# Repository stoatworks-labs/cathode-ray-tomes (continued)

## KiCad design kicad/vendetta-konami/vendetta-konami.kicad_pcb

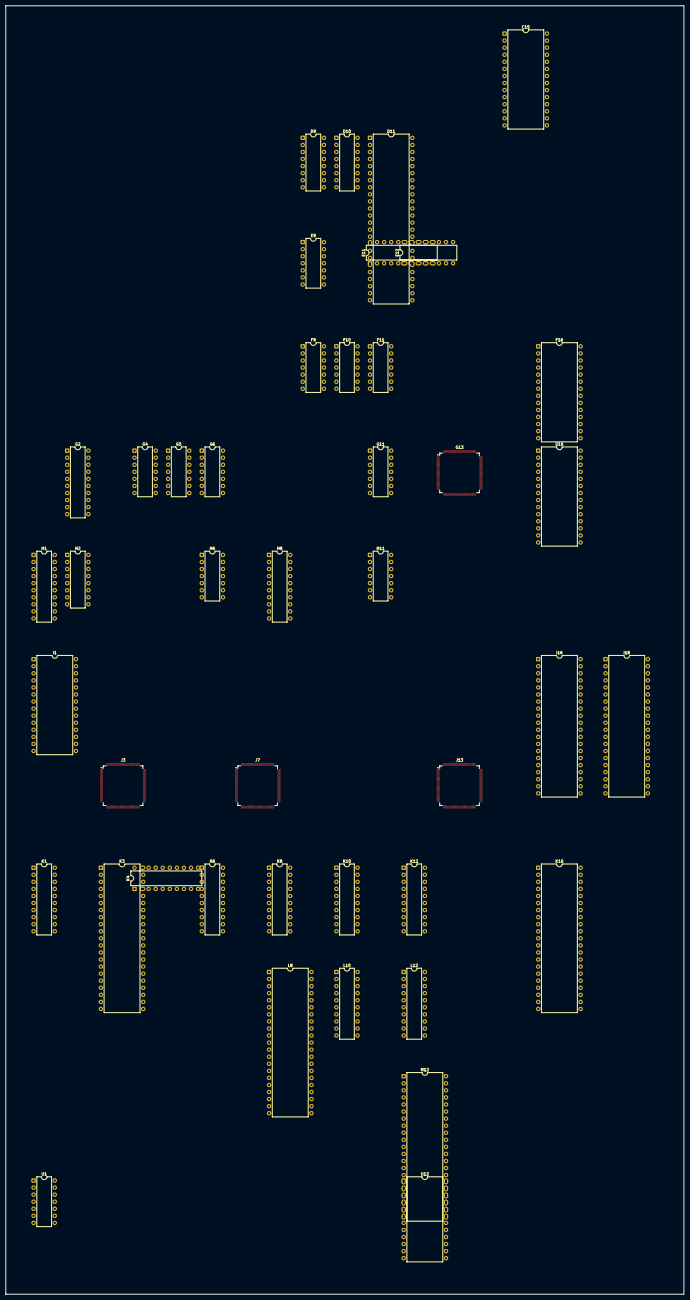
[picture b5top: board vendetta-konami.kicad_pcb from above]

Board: 2 copper layers, 243.9 x 463.4 mm, 43 parts (0 on the bottom side), 315 nets, no tracks yet.

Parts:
C15: DIP-28_W15.24mm
D9: 74LS174; DIP-16_W7.62mm
D10: 74LS138; DIP-16_W7.62mm
D11: DIP-48_W15.24mm
E9: 74LS04; DIP-14_W7.62mm
E11: 74LS273; DIP-20_W7.62mm
E12: 74LS367; DIP-16_W7.62mm
F9, F10: 74LS32; DIP-14_W7.62mm
F11: 74LS04; DIP-14_W7.62mm
F16: MB8464A-10W-15W; DIP-28_W15.24mm
G2: 74LS245; DIP-20_W7.62mm
G4: 74LS04; DIP-14_W7.62mm
G5, G6: 74LS08; DIP-14_W7.62mm
G11: 74LS74; DIP-14_W7.62mm
G13: 052109; TQFP-120_14x14mm_P0.4mm
G16: MB8464A-10W-15W; DIP-28_W15.24mm
H1, H8: 74LS245; DIP-20_W7.62mm
H2: 74LS367; DIP-16_W7.62mm
H6: 74LS32; DIP-14_W7.62mm
H11: 74LS74; DIP-14_W7.62mm
I1: MB8464A-10W-15W; DIP-28_W15.24mm
I16, I18: 955D05-06-07-08; DIP-40_W15.24mm
J3: 053246; TQFP-120_14x14mm_P0.4mm
J7: 053247; TQFP-120_14x14mm_P0.4mm
J13: 051962; TQFP-120_14x14mm_P0.4mm
K1, K4, K6, K8, K10, K12: 74LS374; DIP-20_W7.62mm
K3, K16: 065A08; DIP-42_W15.24mm
L8: 065A08; DIP-42_W15.24mm
L10, L12: 74LS374; DIP-20_W7.62mm
M12: 065A08; DIP-42_W15.24mm
U1: 74LS32; DIP-14_W7.62mm
U12: 051550; DIP-24_W15.24mm

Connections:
/COIN_1: D9.2, U12.15
/COIN_2: D9.5, U12.16
/COIN_CNT_1: U12.20, U12.21
/COIN_CNT_2: U12.22, U12.23
/CPU~RES: D9.1, E11.1, E12.5, G5.4
/CR~CS: D10.11, J7.9
/DS: H6.13, U1.13
/IRQEN: E11.16, G5.5
/MAIN_A0: C15.10, D11.42, F9.12, G2.2, G4.3, G13.66, J3.4, J7.4, J13.88
/MAIN_A1: C15.9, D10.1, D11.41, G13.67, J3.7, J7.7, J13.89
/MAIN_A2: C15.8, D10.2, D11.40, G2.4, G13.68, J3.6, J7.6
/MAIN_A3: C15.7, D10.3, D11.38, G2.5, G13.69
/MAIN_A4: C15.6, G2.6, G13.116
/MAIN_A5: G2.7, G13.115
/MAIN_A6: G2.8, G13.114
/MAIN_A7: G2.9, G13.113
/MAIN_A8: G13.112, H2.2
/MAIN_A9: G13.111, H2.4
/MAIN_A10: G13.110, H2.6
/MAIN_A11: G13.109, H2.10
/MAIN_A12: G13.80, H2.12
/MAIN_DB0: C15.11, D9.14, D11.21, E11.18, G13.56, H1.2, J7.30, J13.79
/MAIN_DB1: C15.12, D9.13, D11.20, E11.17, G13.57, H1.3, J7.29, J13.80
/MAIN_DB2: C15.13, D9.11, D11.19, E11.14, G13.58, H1.4, J7.28, J13.81
/MAIN_DB3: C15.15, D9.6, D11.18, E11.13, G13.59, H1.5, J7.27, J13.82
/MAIN_DB4: C15.16, D9.4, D11.16, E11.8, G13.60, H1.6, J7.26, J13.83
/MAIN_DB5: C15.17, D9.3, D11.15, E11.7, G13.62, H1.7, J7.25, J13.84
/MAIN_DB6: C15.18, D11.14, E11.4, G13.63, H1.8, J7.24
/MAIN_DB7: C15.19, D11.13, E11.3, G13.64, H1.9, J7.23, J13.86
/M~RESET: E12.4, G13.98
/OBJCHA: D9.15, G4.1
/OBJCLK6: J3.12, J7.12, J13.78
/OBJCLK12: J3.10, J7.10, J13.95
/RMRD: D9.10, G13.97, J13.96
/SCR~CLK: F11.8, G13.65, J13.90
/SYS~RES: D11.7, G11.9, G13.55, J3.3, J7.3, J13.92
/VBLK: E9.8, H11.3, H11.11
/VRAM~CS: G13.54, G13.84, J13.97
/objects/EA0: G2.18, I1.10, J3.113
/objects/EA1: G2.17, I1.9, J3.112
/objects/EA2: G2.16, I1.8, J3.110
/objects/EA3: G2.15, I1.7, J3.109
/objects/EA4: H2.11, I1.2, J3.108
/objects/EN0: G2.14, I1.6, J3.105
/objects/EN1: G2.13, I1.5, J3.104
/objects/EN2: G2.12, I1.4, J3.103
/objects/EN3: G2.11, I1.3, J3.102
/objects/EN4: H2.3, I1.25, J3.100
/objects/EN5: H2.5, I1.24, J3.99
/objects/EN6: H2.7, I1.21, J3.98
/objects/EN7: H2.9, I1.23, J3.97
/objects/G2D0: J3.32, J7.119
/objects/G2D1: J3.33, J7.118
/objects/G2D2: J3.34, J7.117
/objects/G2D3: J3.35, J7.116
/objects/G2D4: J3.36, J7.115
/objects/G2D5: J3.37, J7.114
/objects/G2D6: J3.38, J7.113
/objects/G2D7: J3.39, J7.112
/objects/G2D8: J3.40, J7.110
/objects/G2D9: J3.42, J7.109
/objects/G2D10: J3.43, J7.108
/objects/G2D11: J3.44, J7.107
/objects/G2D12: J3.45, J7.105
/objects/G2D13: J3.47, J7.104
/objects/G2D14: J3.48, J7.103
/objects/G2D15: J3.49, J7.102
/objects/G2D16: J3.50, J7.100
/objects/G2D17: J3.52, J7.99
/objects/G2D18: J3.53, J7.98
/objects/G2D19: J3.54, J7.97
/objects/G2D20: J3.55, J7.96
/objects/G2D21: J3.56, J7.95
/objects/LUTD0: H1.18, I1.11, J3.30
/objects/LUTD1: H1.17, I1.12, J3.29
/objects/LUTD2: H1.16, I1.13, J3.28
/objects/LUTD3: H1.15, I1.15, J3.27
/objects/LUTD4: H1.14, I1.16, J3.26
/objects/LUTD5: H1.13, I1.17, J3.25
/objects/LUTD6: H1.12, I1.18, J3.24
/objects/LUTD7: H1.11, I1.19, J3.23
/objects/OBJROMA0: J3.68, K3.10, K16.10, L8.10, M12.10
/objects/OBJROMA1: J3.69, K3.9, K16.9, L8.9, M12.9
/objects/OBJROMA2: J3.70, K3.8, K16.8, L8.8, M12.8
/objects/OBJROMA3: J3.72, K3.7, K16.7, L8.7, M12.7
/objects/OBJROMA4: J3.73, K3.6, K16.6, L8.6, M12.6
/objects/OBJROMA5: J3.74, K3.5, K16.5, L8.5, M12.5
/objects/OBJROMA6: J3.75, K3.4, K16.4, L8.4, M12.4
/objects/OBJROMA7: J3.77, K3.3, K16.3, L8.3, M12.3
/objects/OBJROMA8: J3.78, K3.41, K16.41, L8.41, M12.41
/objects/OBJROMA9: J3.79, K3.40, K16.40, L8.40, M12.40
/objects/OBJROMA10: J3.80, K3.39, K16.39, L8.39, M12.39
/objects/OBJROMA11: J3.82, K3.38, K16.38, L8.38, M12.38
/objects/OBJROMA12: J3.83, K3.37, K16.37, L8.37, M12.37
/objects/OBJROMA13: J3.84, K3.36, K16.36, L8.36, M12.36
/objects/OBJROMA14: J3.85, K3.35, K16.35, L8.35, M12.35
/objects/OBJROMA15: J3.86, K3.34, K16.34, L8.34, M12.34
/objects/OBJROMA16: J3.87, K3.33, K16.33, L8.33, M12.33
/objects/OBJROMA17: J3.88, K3.2, K16.2, L8.2, M12.2
/objects/OBJROMA18: J3.89, K3.1, K16.1, L8.1, M12.1
/objects/OBJROMA19: J3.90, K3.42, K16.42, L8.42, M12.42
/objects/OBJROMD'0: J7.72, K1.2, K6.2, L10.2, L12.2
/objects/OBJROMD'1: J7.73, K1.5, K6.5, L10.5, L12.5
/objects/OBJROMD'2: J7.74, K1.6, K6.6, L10.6, L12.6
/objects/OBJROMD'3: J7.75, K1.9, K6.9, L10.9, L12.9
/objects/OBJROMD'4: J7.77, K1.12, K6.12, L10.12, L12.12
/objects/OBJROMD'5: J7.78, K1.15, K6.15, L10.15, L12.15
/objects/OBJROMD'6: J7.79, K1.16, K6.16, L10.16, L12.16
/objects/OBJROMD'7: J7.80, K1.19, K6.19, L10.19, L12.19
/objects/OBJROMD'8: J7.82, K4.2, K8.2, K10.2, K12.2
/objects/OBJROMD'9: J7.83, K4.5, K8.5, K10.5, K12.5
/objects/OBJROMD'10: J7.84, K4.6, K8.6, K10.6, K12.6
/objects/OBJROMD'11: J7.85, K4.9, K8.9, K10.9, K12.9
/objects/OBJROMD'12: J7.86, K4.12, K8.12, K10.12, K12.12
/objects/OBJROMD'13: J7.87, K4.15, K8.15, K10.15, K12.15
/objects/OBJROMD'14: J7.88, K4.16, K8.16, K10.16, K12.16
/objects/OBJROMD'15: J7.89, K4.19, K8.19, K10.19, K12.19
/objects/ROMD0: K1.3, K3.14
/objects/ROMD1: K1.4, K3.16
/objects/ROMD2: K1.7, K3.18
/objects/ROMD3: K1.8, K3.20
/objects/ROMD4: K1.13, K3.23
/objects/ROMD5: K1.14, K3.25
/objects/ROMD6: K1.17, K3.27
/objects/ROMD7: K1.18, K3.29
/objects/ROMD8: K3.15, K4.3
/objects/ROMD9: K3.17, K4.4
/objects/ROMD10: K3.19, K4.7
/objects/ROMD11: K3.21, K4.8
/objects/ROMD12: K3.24, K4.13
/objects/ROMD13: K3.26, K4.14
/objects/ROMD14: K3.28, K4.17
/objects/ROMD15: K3.30, K4.18
/objects/ROMD16: K6.3, L8.14
/objects/ROMD17: K6.4, L8.16
/objects/ROMD18: K6.7, L8.18
/objects/ROMD19: K6.8, L8.20
/objects/ROMD20: K6.13, L8.23
/objects/ROMD21: K6.14, L8.25
/objects/ROMD22: K6.17, L8.27
/objects/ROMD23: K6.18, L8.29
/objects/ROMD24: K8.3, L8.15
/objects/ROMD25: K8.4, L8.17
/objects/ROMD26: K8.7, L8.19
/objects/ROMD27: K8.8, L8.21
/objects/ROMD28: K8.13, L8.24
/objects/ROMD29: K8.14, L8.26
/objects/ROMD30: K8.17, L8.28
/objects/ROMD31: K8.18, L8.30
/objects/ROMD32: L10.3, M12.14
/objects/ROMD33: L10.4, M12.16
/objects/ROMD34: L10.7, M12.18
/objects/ROMD35: L10.8, M12.20
/objects/ROMD36: L10.13, M12.23
/objects/ROMD37: L10.14, M12.25
/objects/ROMD38: L10.17, M12.27
/objects/ROMD39: L10.18, M12.29
/objects/ROMD40: K10.3, M12.15
/objects/ROMD41: K10.4, M12.17
/objects/ROMD42: K10.7, M12.19
/objects/ROMD43: K10.8, M12.21
/objects/ROMD44: K10.13, M12.24
/objects/ROMD45: K10.14, M12.26
/objects/ROMD46: K10.17, M12.28
/objects/ROMD47: K10.18, M12.30
/objects/ROMD48: K16.14, L12.3
/objects/ROMD49: K16.16, L12.4
/objects/ROMD50: K16.18, L12.7
/objects/ROMD51: K16.20, L12.8
/objects/ROMD52: K16.23, L12.13
/objects/ROMD53: K16.25, L12.14
/objects/ROMD54: K16.27, L12.17
/objects/ROMD55: K16.29, L12.18
/objects/ROMD56: K12.3, K16.15
/objects/ROMD57: K12.4, K16.17
/objects/ROMD58: K12.7, K16.19
/objects/ROMD59: K12.8, K16.21
/objects/ROMD60: K12.13, K16.24
/objects/ROMD61: K12.14, K16.26
/objects/ROMD62: K12.17, K16.28
/objects/ROMD63: K12.18, K16.30
/objects/SCK: J3.66, K1.11, K4.11, K6.11, K8.11, K10.11, K12.11, L10.11, L12.11
/objects/~RDB: H2.13, I1.22, J3.114
/objects/~REG: J3.2, J7.2, U1.11
/objects/~SET0: J3.65, J7.90, K1.1, K4.1
/objects/~SET1: J3.64, J7.92, K6.1, K8.1
/objects/~SET2: J3.63, J7.93, K10.1, L10.1
/objects/~SET3: J3.62, J7.94, K12.1, L12.1
/scroll/CAB1: G13.23, H8.12
/scroll/CAB2: G13.22, H8.11
/scroll/COL2: G13.39, H8.18
/scroll/COL3: G13.40, H8.17
/scroll/COL4: G13.41, H8.16
/scroll/COL5: G13.42, H8.15
/scroll/COL6: G13.43, H8.14
/scroll/COL7: G13.46, H8.13
/scroll/COLB5: H8.6, J13.109
/scroll/COLB6: H8.7, J13.108
/scroll/COLB7: H8.9, J13.107
/scroll/GFXROMA0: G13.35, I16.9, I18.9
/scroll/GFXROMA1: G13.34, I16.8, I18.8
/scroll/GFXROMA2: G13.33, I16.7, I18.7
/scroll/GFXROMA3: G13.32, I16.6, I18.6
/scroll/GFXROMA4: G13.30, I16.5, I18.5
/scroll/GFXROMA5: G13.29, I16.4, I18.4
/scroll/GFXROMA6: G13.28, I16.3, I18.3
/scroll/GFXROMA7: G13.27, I16.2, I18.2
/scroll/GFXROMA8: G13.26, I16.40, I18.40
/scroll/GFXROMA9: G13.25, I16.39, I18.39
/scroll/GFXROMA10: G13.24, I16.38, I18.38
/scroll/GFXROMA11: G13.37, I16.37, I18.37
/scroll/GFXROMA12: G13.38, I16.36, I18.36
/scroll/GFXROMA13: H8.4, I16.35, I18.35
/scroll/GFXROMA14: H8.5, I16.34, I18.34
/scroll/GFXROMA15: H8.2, I16.33, I18.33
/scroll/GFXROMA16: H8.3, I16.32, I18.32
/scroll/GFXROMA17: H8.8, I16.1, I18.1
/scroll/GFXROMD0: I18.13, J13.29
/scroll/GFXROMD1: I18.15, J13.28
/scroll/GFXROMD2: I18.17, J13.27
/scroll/GFXROMD3: I18.19, J13.26
/scroll/GFXROMD4: I18.22, J13.25
/scroll/GFXROMD5: I18.24, J13.24
/scroll/GFXROMD6: I18.26, J13.23
/scroll/GFXROMD7: I18.28, J13.22
/scroll/GFXROMD8: I18.14, J13.21
/scroll/GFXROMD9: I18.16, J13.20
/scroll/GFXROMD10: I18.18, J13.19
/scroll/GFXROMD11: I18.20, J13.18
/scroll/GFXROMD12: I18.23, J13.17
/scroll/GFXROMD13: I18.25, J13.16
/scroll/GFXROMD14: I18.27, J13.13
/scroll/GFXROMD15: I18.29, J13.12
/scroll/GFXROMD16: I16.13, J13.11
/scroll/GFXROMD17: I16.15, J13.10
/scroll/GFXROMD18: I16.17, J13.9
/scroll/GFXROMD19: I16.19, J13.8
/scroll/GFXROMD20: I16.22, J13.7
/scroll/GFXROMD21: I16.24, J13.6
/scroll/GFXROMD22: I16.26, J13.5
/scroll/GFXROMD23: I16.28, J13.4
/scroll/GFXROMD24: I16.14, J13.3
/scroll/GFXROMD25: I16.16, J13.2
/scroll/GFXROMD26: I16.18, J13.120
/scroll/GFXROMD27: I16.20, J13.119
/scroll/GFXROMD28: I16.23, J13.118
/scroll/GFXROMD29: I16.25, J13.117
/scroll/GFXROMD30: I16.27, J13.116
/scroll/GFXROMD31: I16.29, J13.115
/scroll/PREPE: E12.6, G13.90
/scroll/PREPQ: E12.2, G13.89
/scroll/SCRAMA0: F16.10, G13.2, G16.10
/scroll/SCRAMA1: F16.9, G13.120, G16.9
/scroll/SCRAMA2: F16.8, G13.119, G16.8
/scroll/SCRAMA3: F16.7, G13.118, G16.7
/scroll/SCRAMA4: F16.6, G13.117, G16.6
/scroll/SCRAMA5: F16.5, G13.70, G16.5
/scroll/SCRAMA6: F16.4, G13.71, G16.4
/scroll/SCRAMA7: F16.3, G13.72, G16.3
/scroll/SCRAMA8: F16.25, G13.73, G16.25
/scroll/SCRAMA9: F16.24, G13.76, G16.24
/scroll/SCRAMA10: F16.21, G13.77, G16.21
/scroll/SCRAMA11: F16.23, G13.78, G16.23
/scroll/SCRAMA12: F16.2, G13.79, G16.2
/scroll/S~RESET: E12.10, J13.93
/scroll/VD0: G13.20, G16.11
/scroll/VD1: G13.19, G16.12
/scroll/VD2: G13.18, G16.13
/scroll/VD3: G13.17, G16.15
/scroll/VD4: G13.16, G16.16
/scroll/VD5: G13.13, G16.17
/scroll/VD6: G13.12, G16.18
/scroll/VD7: G13.11, G16.19
/scroll/VD8: F16.11, G13.10
/scroll/VD9: F16.12, G13.9
/scroll/VD10: F16.13, G13.8
/scroll/VD11: F16.15, G13.7
/scroll/VD12: F16.16, G13.6
/scroll/VD13: F16.17, G13.5
/scroll/VD14: F16.18, G13.4
/scroll/VD15: F16.19, G13.3
/scroll/ZA1H: G13.50, J13.101
/scroll/ZA2H: G13.51, J13.100
/scroll/ZA4H: G13.52, J13.99
/scroll/ZB1H: G13.47, J13.106
/scroll/ZB2H: G13.48, J13.103
/scroll/ZB4H: G13.49, J13.102
/scroll/~BE: G13.53, J13.98
/scroll/~RCS1: F16.20, G13.93
/scroll/~ROE1: F16.22, G13.95
/scroll/~ROE2: G13.96, G16.22
/scroll/~RWE1: F16.27, G13.107
/scroll/~RWE2: G13.108, G16.27
/scroll/~VSYNC: H11.10, J13.72
/~CPU: G2.19, H2.1, H2.15, J3.116
/~HSYNC: G6.5, J13.73
/~RD: G13.85, H1.1, H2.14, J13.87
/~VBLANK: J3.119, J13.69
/~WR: C15.27, D11.37
/~XSYNC: G6.6, J3.8, J7.8
unnamed: C15.26, E9.6
unnamed: D9.9, D10.15
unnamed: D10.14, E11.11
unnamed: D11.27, E9.9
unnamed: F10.1, G4.4
unnamed: F9.13, F10.2
unnamed: F11.9, F11.13
unnamed: F11.12, G11.11
unnamed: G11.12, G11.13, U12.10
unnamed: G5.6, H11.4
unnamed: G6.4, H11.9
unnamed: H6.11, I1.27
unnamed: G4.2, J3.9
VCC: C15.20, C15.28, D10.6, D11.17, D11.23, D11.39, D11.43, E12.16, F16.26, F16.28, G2.1, G11.10, G13.14, G13.44, G13.74, G13.104, G16.26, G16.28, H2.16, H11.1, H11.13, I1.26, I1.28, I16.21, I18.21, J3.5, J3.16, J3.46, J3.60, J3.76, J3.106, J3.120, J7.5, J7.16, J7.46, J7.60, J7.70, J7.76, J7.106, J7.120, J13.14, J13.44, J13.74, J13.104, K3.22, K3.32, K16.22, K16.32, L8.22, L8.32, M12.22, M12.32
VSS: C15.14, D11.6, D11.22, D11.28, E12.1, E12.8, F16.14, G13.1, G13.15, G13.21, G13.31, G13.36, G13.45, G13.61, G13.75, G13.91, G13.105, G16.14, G16.20, H2.8, H8.1, H8.19, H11.2, H11.12, I1.14, I1.20, I16.10, I16.11, I16.12, I16.30, I16.31, I18.10, I18.11, I18.12, I18.30, I18.31, J3.91, J3.101, J3.111, J3.117, J3.118, J7.1, J7.11, J7.21, J7.31, J7.41, J7.51, J7.61, J7.62, J7.63, J7.64, J7.65, J7.66, J7.67, J7.68, J7.69, J7.71, J7.81, J7.91, J7.101, J7.111, J13.1, J13.15, J13.31, J13.45, J13.61, J13.75, J13.91, J13.94, J13.105, J13.110, J13.111, J13.112, J13.113, J13.114, K3.11, K3.12, K3.13, K3.31, K16.11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

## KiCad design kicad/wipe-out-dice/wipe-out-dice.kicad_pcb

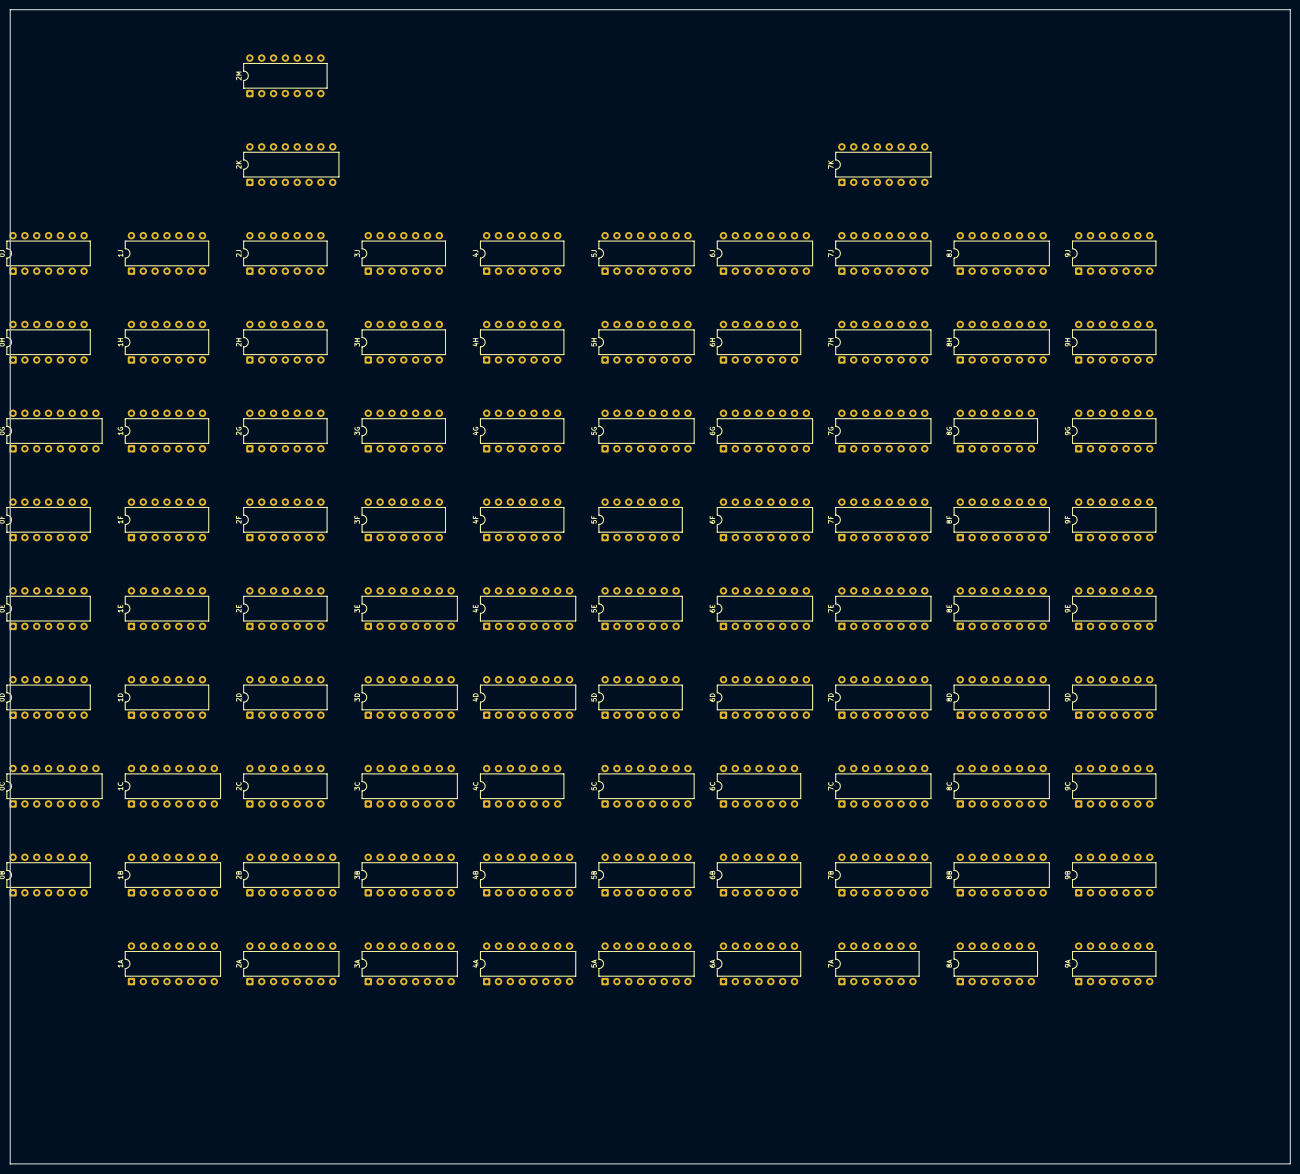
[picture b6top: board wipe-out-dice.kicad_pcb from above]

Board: 2 copper layers, 274.6 x 247.6 mm, 92 parts (0 on the bottom side), 339 nets, no tracks yet.

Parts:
0B, 2C, 2H, 4C, 6A, 6C, 8A: 7404; DIP-14_W7.62mm
0C, 0G, 1C, 2K, 5H, 5J, 6J, 7B, 7K, 8F: 74S112; DIP-16_W7.62mm
0D: 7437; DIP-14_W7.62mm
0E, 3H: 7486; DIP-14_W7.62mm
0F, 0H, 1H, 2M, 3J, 4G, 6H, 9D, 9E: 7402; DIP-14_W7.62mm
0J, 3G, 7A, 9B, 9C: 7420; DIP-14_W7.62mm
1A, 1B, 2A, 2B, 3A, 3B, 3C, 3D, 3E, 6D, 6E, 6F, 6G, 7C, 7D, 7E, 7J, 8D, 8E: 74161; DIP-16_W7.62mm
1D, 1F, 2D, 4H, 5E, 6B, 8G, 9A, 9F, 9G, 9H, 9J: 7400; DIP-14_W7.62mm
1E, 1J, 3F, 4F, 4J, 5F: 7427; DIP-14_W7.62mm
1G, 2G, 2J: 7408; DIP-14_W7.62mm
2E, 2F, 5D: 7421; DIP-14_W7.62mm
4A, 4B, 5B, 5C: 74153; DIP-16_W7.62mm
4D, 7G: 82S123; DIP-16_W7.62mm
4E: 74166; DIP-16_W7.62mm
5A, 5G, 8B, 8C, 8J: 74174; DIP-16_W7.62mm
7F, 7H, 8H: 74157; DIP-16_W7.62mm

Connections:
+5V: 0B.14, 0C.16, 0D.14, 0E.14, 0F.14, 0G.16, 0H.14, 0J.14, 1A.16, 1B.16, 1C.16, 1D.14, 1E.14, 1F.14, 1G.14, 1H.14, 1J.14, 2A.16, 2B.16, 2C.14, 2D.14, 2E.14, 2F.14, 2G.14, 2H.14, 2J.14, 2K.16, 2M.14, 3A.16, 3B.16, 3C.16, 3D.16, 3E.16, 3F.14, 3G.14, 3H.14, 3J.14, 4A.16, 4B.16, 4C.14, 4D.16, 4E.16, 4F.14, 4G.14, 4H.14, 4J.14, 5A.16, 5B.16, 5C.16, 5D.14, 5E.14, 5F.14, 5G.16, 5H.16, 5J.16, 6A.14, 6B.14, 6C.14, 6D.16, 6E.16, 6F.16, 6G.16, 6H.14, 6J.16, 7A.14, 7B.16, 7C.16, 7D.16, 7E.16, 7F.16, 7G.16, 7H.16, 7J.16, 7K.16, 8A.14, 8B.16, 8C.16, 8D.16, 8E.16, 8F.16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
GND: 0B.7, 0C.8, 0D.7, 0E.7, 0F.7, 0G.8, 0H.7, 0J.7, 1A.3, 1A.4, 1A.5, 1A.8, 1B.5, 1B.8, 1C.8, 1D.7, 1E.7, 1F.7, 1G.7, 1H.7, 1J.7, 2A.3, 2A.4, 2A.5, 2A.8, 2B.3, 2B.8, 2C.7, 2D.7, 2E.7, 2F.7, 2G.7, 2H.7, 2J.7, 2K.8, 2M.7, 3A.3, 3A.5, 3A.8, 3B.3, 3B.5, 3B.8, 3C.3, 3C.5, 3C.8, 3D.3, 3D.5, 3D.8, 3E.3, 3E.4, 3E.5, 3E.6, 3E.8, 3F.7, 3G.7, 3H.7, 3J.7, 4A.1, 4A.8, 4A.15, 4B.1, 4B.8, 4C.7, 4C.13, 4D.8, 4D.15, 4E.1, 4E.2, 4E.3, 4E.4, 4E.5, 4E.8, 4E.14, 4F.7, 4G.7, 4H.7, 4J.7, 5A.8, 5B.8, 5C.1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
VCC: 0C.2, 0C.3, 0C.4, 0C.10, 0C.15, 0G.4, 0G.10, 1A.1, 1A.6, 1A.7, 1A.10, 1B.1, 1C.4, 1C.10, 1C.14, 1C.15, 2A.1, 2A.7, 2A.10, 2B.1, 3A.1, 3A.6, 3A.10, 3B.1, 3B.6, 3B.10, 3C.1, 3C.6, 3C.10, 3D.1, 3D.6, 3D.10, 3E.1, 5A.1, 5H.4, 5H.10, 5H.14, 5H.15, 5J.4, 5J.10, 5J.14, 5J.15, 6D.1, 6D.10, 6E.1, 6E.10, 6F.1, 6F.10, 6G.1, 6G.10, 6J.3, 6J.10, 7B.4, 7B.14, 7C.1, 7D.1, 7E.1, 7J.1, 8B.1, 8C.1, 8D.1, 8E.1, 8J.1
_1BEGD: 8A.8, 9C.1, 9C.2
_1BLGD: 8A.10, 8B.13, 9A.1, 9J.9
_1BLGE: 3H.12, 8B.12, 9C.4, 9J.2
_1BVAF: 2J.10, 2J.13, 8A.12, 9G.1, 9G.5
_1EBCA: 7C.9, 8B.15
_1NCFG: 2H.8, 5H.2
_1PCX3: 5A.4, 6B.11
_1PGCC: 5E.12, 8C.15
_1PGSB: 5H.3, 6A.6
_1TCKG: 2M.11, 6A.2
_1TECC: 0B.10, 1C.2, 1C.3
_1TEG7: 0H.6, 1J.5, 2C.8, 2F.5, 3F.4, 8H.6
_1TLCC: 0B.12, 1C.11, 1C.12, 7C.7
_1TLG7: 0H.8, 1J.13, 2C.10, 2F.9, 3F.2, 8H.13
_1TNSC: 2H.6, 4A.14, 4B.14
_1TPSC: 2H.4, 5B.14, 5C.14
_1TQ05: 0C.5, 0D.1, 0D.2, 9F.9
_2KQEA: 6J.1, 9D.1
_2KQEL: 8F.1, 9D.10, 9D.11
_2KQLN: 8F.13, 9D.4, 9D.12
_2THSC: 0D.11, 0G.13, 1C.13, 2K.1, 2K.13
_2TQ05: 0C.13, 0D.6, 0G.1, 1C.1, 5H.1, 6J.13, 7B.1, 7B.13, 7K.1, 7K.13
_5BDEC: 8G.5, 8H.7
_5BDGD: 9J.4, 9J.8
_5BDGR: 9J.3, 9J.5
_5BDLC: 8G.12, 8H.12
_5BDRD: 8D.5, 8F.7
_5BDRR: 7D.5, 8F.6
_5BDSD: 8F.10, 8G.8
_5BDSL: 8F.15, 8G.6
_5BDSR: 8F.4, 8G.3
_5BDSU: 8F.14, 8G.11
_5BECB: 8A.4, 8C.3
_5BECL: 7E.9, 9C.6
_5BEGA: 8C.2, 8C.4, 9A.5, 9B.5
_5BEGB: 8C.5, 8C.6, 9B.4
_5BEGC: 8C.7, 8C.11, 9B.2
_5BEGD: 8A.9, 8C.10, 9A.4, 9B.1
_5BLCB: 8A.6, 8B.3
_5BLCL: 8E.9, 9A.3
_5BLGA: 8B.2, 8B.4, 9A.9, 9B.9
_5BLGB: 8B.5, 8B.6, 9B.10
_5BLGC: 8B.7, 8B.11, 9B.12
_5BLGD: 8A.11, 8B.10, 9A.10, 9B.13
_5BSCG: 9E.3, 9H.3
_5BVAD: 9A.11, 9C.10
_5BVAF: 3G.10, 8A.13, 9C.8, 9E.5, 9E.9
_5EBCA: 6A.12, 9D.3
_5EBEA: 6B.3, 7A.5
_5EBEB: 6B.6, 7A.4
_5EBEC: 6B.8, 7A.1, 7A.2
_5EBIP: 7A.9, 7B.6, 7J.10
_5EBOP: 6J.7, 7A.10
_5EBUZ: 6J.15, 7A.12, 7A.13, 7B.7, 7D.9, 7J.9, 8D.9, 9C.12
_5KAAA: 3G.12, 4G.10, 9E.6
_5KAAB: 3G.13, 4G.13, 9E.8
_5KAAE: 8J.3, 9G.3
_5KAAF: 8J.4, 9G.6
_5KABC: 6A.8, 9D.5, 9F.12
_5KABD: 6A.10, 9D.9, 9F.13
_5KABE: 8J.2, 9F.5, 9H.4
_5KABF: 8J.5, 9F.4, 9H.10
_5KACG: 3F.1, 4F.3, 9F.2, 9G.8
_5KACH: 3F.3, 3F.11, 9F.1, 9G.11
_5KBCH: 6H.10, 9H.5
_5KBDG: 6H.13, 9H.9
_5NCAD: 3J.12, 4J.12
_5NCCC: 1F.11, 3E.7, 3E.10, 4E.9
_5NCCE: 2C.12, 4E.6
_5NCFA: 3J.9, 4J.8
_5NCFB: 3J.8, 4H.6, 9H.12
_5NCFE: 3J.11, 4H.8, 9H.13
_5NCFG: 2H.9, 3J.4
_5NCG2: 4C.10, 5D.10
_5NCG3: 4C.8, 5D.4
_5NCGA: 4H.3, 5D.1, 5D.2, 5D.12, 5D.13
_5NCS0: 4C.6, 4D.12
_5NCS1: 4C.4, 4D.13
_5NCS2: 4C.2, 4D.14
_5PCBB: 5F.13, 7K.7
_5PCLB: 2K.6, 4F.9
_5PCRB: 2K.7, 5F.5
_5PCS3: 6C.12, 8F.2, 8F.12
_5PCTB: 5F.9, 7K.6
_5PCX3: 2M.10, 6B.12, 6B.13
_5PDEC: 5E.8, 9C.5
_5PDGS: 2M.9, 3H.10, 5B.1, 5B.15, 5E.5, 5E.9, 6J.6
_5PDLC: 5E.6, 9A.2
_5PDPS: 5E.10, 6C.10
_5PGCC: 4G.6, 5J.6
_5PGCE: 5J.7, 6H.2
_5PGCG: 1E.2, 4J.1, 4J.11, 5H.7
_5PGSB: 5E.3, 6A.5
_5PGSC: 5H.6, 9E.11
_5PGSR: 3A.9, 3B.9, 3C.9, 3D.9, 5E.11, 7B.10
_5PJC1: 5A.13, 6A.4
_5PKE5: 6C.6, 7K.4, 7K.10
_5PKE8: 6C.2, 7K.14, 7K.15
_5PKL5: 2K.4, 2K.10, 6C.8
_5PKL8: 2K.14, 2K.15, 6C.4
_5TCBL: 0H.13, 4H.12
_5TCKG: 6A.1, 8H.1, 9E.2, 9J.11
_5TEC0: 2C.2, 8H.5
_5TEC5: 0C.11, 2C.4
_5TEC8: 0G.15, 1B.3, 1B.4, 1B.6, 1C.6
_5TECC: 0B.11, 1A.9, 1B.9, 1D.3
_5TECD: 1D.6, 1D.10, 1D.12
_5TEG7: 1D.8, 1G.10, 1J.9, 2C.9, 3F.10, 8H.3
_5TEG8: 1D.11, 7E.7, 7E.10
_5TELA: 0F.3, 1F.3
_5TGBG: 1H.6, 4J.6
_5TGLG: 1H.2, 1J.6
_5TGRG: 1H.3, 1J.8
_5TGTG: 1H.5, 1J.12
_5THBG: 0G.6, 2M.2
_5THPG: 0J.8, 1H.12
_5THSC: 0C.7, 1F.9
_5TLC0: 2C.6, 8H.14
_5TLC8: 0G.14, 1C.7, 2B.4, 2B.5, 2B.6, 3G.4, 3G.5, 7C.10
_5TLCC: 0B.13, 2A.9, 2B.9, 2D.3
_5TLCD: 2D.6, 2D.10, 2D.12
_5TLG7: 1G.13, 2C.11, 2D.8, 4F.4, 4J.5, 8H.10
_5TLG8: 2D.11, 8E.7, 8E.10
_5TLLA: 0F.6, 1F.6
_5TLLG: 2H.2, 5B.2, 5C.2
_5TNSC: 2H.5, 3J.1
_5TPSC: 1E.12, 2H.3
_5TVBG: 0G.7, 2M.5
_5TVPG: 0J.6, 1H.9
_5TVSC: 1F.10, 3G.6
_5VDAC: 3G.9, 4F.12
_5VDAE: 4H.11, 8J.13
_5VDAF: 2H.13, 8J.12
_6KQCA: 9D.6, 9D.8, 9F.8
_6THSC: 0D.8, 0D.12, 0D.13, 2A.2, 2B.2, 3E.2, 6E.2, 6F.2, 7C.2, 8B.9, 8D.2, 8E.2
_6TQ05: 0D.3, 0D.4, 0D.5, 1A.2, 1B.2, 3A.2, 3B.2, 3C.2, 3D.2, 5G.9, 6D.2, 6G.2, 7D.2, 7E.2, 7J.2, 8C.9, 8J.9, 9D.2
_7KQPD: 5A.9, 9D.13
_9X7PT: 3A.4, 3B.4, 3C.4, 3D.4
_BDEC: 8G.2, 8H.4
_BDLC: 8G.9, 8H.9
_BDRD: 8D.3, 8D.4, 8D.6, 8F.9, 9J.10
_BDRR: 7D.3, 7D.4, 7D.6, 8F.5, 9J.1
_BECA: 7D.7, 7D.10, 7E.15
_BECB: 7D.15, 8A.3
_BGS0: 7F.9, 7G.10
_BGS1: 7F.7, 7G.11
_BGS2: 7F.4, 7G.12
_BGS3: 7G.13, 9J.6
_BLCA: 8D.7, 8D.10, 8E.15
_BLCB: 8A.5, 8D.15
_BPE0: 7G.5, 7H.13
_BPE1: 7G.6, 7H.10
_BPE2: 7G.7, 7H.6
_BPE3: 7G.9, 7H.3
_BPL0: 7G.1, 7H.14
_BPL1: 7G.2, 7H.11
_BPL2: 7G.3, 7H.5
_BPL3: 7G.4, 7H.2
_BPS0: 7E.3, 7H.12, 8E.3
_BPS1: 7E.4, 7H.9, 8E.4
_BPS2: 7E.5, 7H.7, 8E.5
_BPS3: 7E.6, 7H.4, 8E.6
_BPSC: 3H.11, 7F.1, 7H.1
_BPSV: 3H.8, 3H.13
_BSC3: 7F.6, 7J.13
_BSC4: 7J.12, 9H.1, 9H.2
_BSCD: 8H.15, 9E.1
_BVAA: 9A.6, 9A.12
_BVAB: 9A.8, 9A.13
_BVAC: 9B.6, 9C.9
_BVAE: 9B.8, 9C.13
_BXYZ: 7F.10, 9H.11
_EBC2: 6J.12, 7B.2, 7C.12
_EBCA: 2M.12, 6A.13, 7A.8, 8B.14
_EBCC: 7B.12, 7C.15
_EBIP: 6B.2, 7B.5
_EBOP: 6B.5, 6J.9
_EBUZ: 6B.9, 7B.9, 9E.12
_KAAC: 5G.13, 9E.4
_KAAD: 5G.14, 9E.10
_KAAG: 2J.8, 8J.6
_KAAH: 2J.11, 8J.11
_KABC: 5G.12, 6A.9, 6H.9
_KABD: 5A.3, 5G.15, 6A.11, 6H.12
_KABG: 6H.11, 8J.7, 9G.9
_KABH: 6H.8, 8J.10, 9G.12
_KACA: 8G.1, 8G.4, 9H.6
_KACB: 8G.10, 8G.13, 9H.8
_KACE: 6J.11, 9F.6
_KACF: 7B.3, 7J.7, 9F.11
_KADG: 7B.11, 9F.3
_KAYA: 2M.13, 9F.10
_KXYA: 9E.13, 9G.10, 9G.13
_NCB0: 3D.14, 4B.6
_NCB1: 3D.13, 4A.10
_NCB2: 3D.12, 4A.6
_NCBA: 3D.7, 4F.6
_NCBC: 3D.15, 4F.5, 4H.10, 4J.4, 4J.10
_NCC1: 1F.13, 3E.13, 4D.10
_NCC2: 3E.12, 4D.11
_NCC3: 1F.12, 3E.11, 4H.1
_NCCE: 2C.13, 3E.9, 4G.1
_NCFC: 3J.5, 3J.10
_NCFF: 3J.6, 3J.13
_NCG2: 4C.11, 4D.3
_NCG3: 4C.9, 4D.4
_NCG4: 4D.5, 4H.2
_NCG5: 4D.6, 4E.10
_NCG6: 4D.7, 5D.9
_NCG7: 4D.9, 5D.5
_NCH6: 4E.11, 5D.8
_NCH7: 4E.12, 5D.6
_NCL0: 3A.14, 4B.3
_NCL1: 3A.13, 4A.13
_NCL2: 3A.12, 4A.3
_NCLA: 3A.7, 3F.6
_NCLC: 1J.4, 3A.15, 3F.5, 4H.5, 4J.13
_NCR0: 3C.14, 4B.4
_NCR1: 3C.13, 4A.12
_NCR2: 3C.12, 4A.4
_NCRA: 3C.7, 3F.8
_NCRC: 1J.10, 3C.15, 3F.9, 4H.4, 4J.2
_NCS0: 4B.7, 4C.5
_NCS1: 4A.9, 4C.3
_NCS2: 4A.7, 4C.1
_NCSC: 4B.9, 4E.15
_NCT0: 3B.14, 4B.5
_NCT1: 3B.13, 4A.11
_NCT2: 3B.12, 4A.5
_NCTA: 3B.7, 3F.12
_NCTC: 1J.2, 3B.15, 3F.13, 4H.9, 4J.9
_NCVD: 4E.13, 4F.13
_PCB1: 5B.10, 6D.13
_PCB2: 5B.6, 6D.12
_PCB3: 5C.10, 6D.11
_PCBB: 6D.9, 7K.9
_PCBC: 5F.2, 6D.15
_PCBE: 5C.6, 5F.12, 6D.7
_PCL1: 5B.13, 6E.13
_PCL2: 5B.3, 6E.12
_PCL3: 5C.13, 6E.11
_PCLB: 2K.5, 6E.9
_PCLC: 4F.10, 6E.15
_PCLE: 4F.8, 5C.3, 6E.7
_PCR1: 5B.12, 6F.13
_PCR2: 5B.4, 6F.12
_PCR3: 5C.12, 6F.11
_PCRB: 2K.9, 6F.9
_PCRC: 5F.4, 6F.15
_PCRE: 5C.4, 5F.6, 6F.7
_PCS1: 5A.11, 5B.9
_PCS2: 5A.6, 5B.7
_PCS3: 2M.8, 5C.9, 6C.13, 8F.3, 8F.11
_PCSE: 0J.1, 0J.13, 5C.7
_PCT1: 5B.11, 6G.13
_PCT2: 5B.5, 6G.12
_PCT3: 5C.11, 6G.11
_PCTB: 6G.9, 7K.5
_PCTC: 5F.10, 6G.15
_PCTE: 5C.5, 5F.8, 6G.7
_PDGS: 6J.5, 7F.3
_PDPS: 3H.9, 5A.2, 5E.4, 6C.11
_PDS1: 5A.10, 7F.11
_PDS2: 5A.7, 7F.5
_PDS3: 5A.5, 7F.2
_PGCB: 4G.5, 5J.3, 8C.12
_PGCC: 5J.5, 8C.14
_PGCD: 4G.4, 5J.11, 6H.3
_PGCE: 5E.2, 5J.9, 6H.6
_PGCF: 5H.11, 6H.1
_PGCH: 5H.12, 6H.4
_PGSC: 2M.3, 2M.6, 5E.13, 5G.1, 5H.5, 5J.2, 5J.12, 6H.5, 6J.4, 6J.14, 7B.15, 7G.14
_PJC0: 5A.12, 5A.14
_PJC1: 5A.15, 6A.3
_PKE5: 5G.7, 6C.5
_PKE8: 5G.2, 6C.1
_PKL5: 5G.10, 6C.9
_PKL8: 5G.5, 6C.3
_TCSC: 1F.8, 8J.14
_TE43: 0J.5, 3H.3
_TE75: 0E.6, 1E.3, 1G.1
_TE76: 0E.3, 1E.5, 1G.2
_TEC0: 1A.14, 2C.1, 4E.7, 8H.2
_TEC3: 1A.11, 1B.10, 3H.1
_TEC4: 0F.2, 1B.14, 2E.13, 2F.2, 3H.2
_TEC5: 0C.12, 0E.4, 1B.13, 2C.3, 2E.10
_TEC6: 0E.1, 1B.12, 2E.9, 2F.4, 4B.12, 4B.13
_TEC7: 0E.2, 0E.5, 1B.11, 1D.9, 4B.10, 4B.11
_TEC8: 0C.14, 1C.5, 1D.4, 1D.13, 1E.4, 4B.15, 5G.3
_TECA: 1A.15, 1B.7, 1D.1, 1F.2, 2E.12
_TECB: 1B.15, 1D.2, 1D.5, 2J.12
_TEKG: 0H.5, 1G.3, 2G.2, 9J.13
_TELG: 0J.4, 1E.6, 1F.1, 1G.9, 1J.1, 4J.3, 5F.1, 5F.11
_TEVL: 0F.1, 0F.9, 0G.2, 0G.3, 2J.1
_THBG: 0F.8, 0G.5, 0J.2, 2F.1
_THBL: 0F.10, 0H.12
_THCH: 2G.3, 4G.8
_THCL: 2E.6, 2G.1, 2G.5
_THLG: 1H.4, 1H.11, 2J.5
_THLN: 2J.6, 4F.1, 9G.4
_THPD: 1H.13, 4G.12
_THSC: 0C.9, 0D.9, 0D.10
_THYZ: 2G.13, 2M.1
_TL43: 0J.9, 3H.6
_TL75: 0E.11, 1E.11, 1G.4
_TL76: 0E.8, 1E.9, 1G.5
_TLC0: 2A.14, 2C.5, 8H.11
_TLC2: 2A.12, 3G.1
_TLC3: 2A.11, 2B.10, 3H.4, 6B.1
_TLC4: 0F.5, 2B.14, 2E.2, 2F.13, 3H.5, 6B.4
_TLC5: 0E.13, 2B.13, 2E.4, 4G.2
_TLC6: 0E.10, 2B.12, 2E.5, 2F.10, 6B.10
_TLC7: 0E.9, 0E.12, 2B.11, 2D.9
_TLC8: 1C.9, 1E.10, 2A.6, 2D.5, 2D.13, 5G.4, 5H.13, 5J.1, 5J.13
_TLCA: 1F.5, 2A.15, 2B.7, 2D.1, 2E.1
_TLCB: 2B.15, 2D.2, 2D.4, 2J.9, 3G.2
_TLHL: 0F.4, 0F.12, 0G.11, 0G.12, 2J.4
_TLKG: 0H.9, 1G.6, 2G.9, 4A.2, 4B.2, 9J.12
_TLLG: 0J.10, 1E.8, 1F.4, 1G.12, 1J.3, 1J.11, 2H.1, 4F.11, 4G.3, 5F.3
_TNSA: 0H.4, 3J.2
_TNSB: 0H.10, 3J.3
_TPHR: 2G.11, 7K.2, 7K.12
_TPHS: 2F.6, 5G.6
_TPSA: 1E.13, 1G.8
_TPSB: 1E.1, 1G.11
_TPVR: 2G.6, 2K.2, 2K.12
_TPVS: 2F.8, 5G.11
_TVBG: 0F.11, 0G.9, 0J.12, 2F.12
_TVBL: 0F.13, 0H.11
_TVCH: 2G.8, 4G.11
_TVCL: 2E.8, 2G.10, 2G.12
_TVLG: 1H.1, 1H.8, 2J.2
_TVLN: 2J.3, 4F.2, 9G.2
_TVPD: 1H.10, 4G.9
_TVYZ: 2G.4, 2M.4
_VDAD: 3G.8, 4H.13

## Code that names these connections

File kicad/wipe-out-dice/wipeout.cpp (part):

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#define _1TQ05  "0C", 5
#define _6TQ05  "0D", 3  
#define _2TQ05  "0D", 6  
#define _THSC   "0C", 9  //HSYNC 
#define _5THSC  "0C", 7  //HSYNC
#define _6THSC  "0D", 8
#define _2THSC  "0D", 11
#define _TCSC   "1F", 8  //COMP SYNC

  //Timing/Syncing/Blanking
#define _TECA   "1A", 15
#define _TEC0   "1A", 14
#define _TEC3   "1A", 11
#define _TEC4   "1B", 14
#define _TEC5   "1B", 13
#define _TEC6   "1B", 12
#define _TEC7   "1B", 11
#define _TECB   "1B", 15
#define _5TEC0  "2C", 2
#define _5TEC5  "2C", 4
#define _5TECC  "1D", 3
#define _1TECC  "0B", 10
#define _TEC8   "1C", 5
#define _5TEC8  "1C", 6
#define _5TECD  "1D", 6
#define _5TEG7  "1D", 8
#define _5TEG8  "1D", 11
#define _1TEG7  "2C", 8

#define _TLCA   "2A", 15 
#define _TLC0   "2A", 14
#define _TLC2   "2A", 12
#define _TLC3   "2A", 11
#define _TLC4   "2B", 14
#define _TLC5   "2B", 13
#define _TLC6   "2B", 12
#define _TLC7   "2B", 11
#define _TLCB   "2B", 15
#define _5TLC0  "2C", 6
#define _5TLCC  "2D", 3
#define _1TLCC  "0B", 12
#define _TLC8   "1C", 9
#define _5TLC8  "1C", 7
#define _5TLCD  "2D", 6
#define _5TLG8  "2D", 11
#define _5TVSC  "3G", 6   //VERT SYNC
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  // T/B goal gate
#define _TE76   "0E", 3
#define _TE75   "0E", 6
#define _TELG   "1E", 6
#define _5TELA  "1F", 3
#define _TEVL   "0F", 1  
#define _THBG   "0G", 5
#define _5THBG  "0G", 6
#define _THBL   "0F", 10  //HORIZ BLANKING
#define _THYZ   "2M", 1

  // L/R goal gate
#define _TL76   "0E", 8
#define _TL75   "0E", 11
#define _TLLG   "1E", 8
#define _5TLLG  "2H", 2
#define _5TLLA  "1F", 6
#define _TLHL   "0F", 4
#define _TVBG   "0G", 9
#define _5TVBG  "0G", 7
#define _TVBL   "0F", 13  //VERT BLANKING
#define _TVYZ   "2M", 4

  // H/V cross gen
#define _TEKG   "1G", 3
#define _THCL   "2E", 6
#define _TLKG   "1G", 6
#define _1TCKG  "6A", 2
#define _TVCL   "2E", 8
#define _5TCKG  "CAP32", 2
#define _THCH   "2G", 3
#define _TPVR   "2G", 6
#define _TVCH   "2G", 8
#define _TPHR   "2G", 11

  //determine 2/4 players
#define _TPSA   "1G", 8
#define _TPSB   "1G", 11
#define _5TPSC  "1E", 12
#define _1TPSC  "2H", 4  //2 OR 4 PLAYER PAD

  //score enable
#define _TNSA   "0H", 4
#define _TNSB   "0H", 10
#define _5TNSC  "3J", 1
#define _1TNSC  "2H", 6  //SCORE ENABLE

  // H/V paddle
#define _TPHS   "2F", 6  //HORIZ PADDLE
#define _TPVS   "2F", 8  //VERT PADDLE

  // L/R select
#define _TE43   "3H", 3
#define _5TGLG  "1J", 6
#define _5TGRG  "1J", 8
#define _5TVPG  "0J", 6
#define _TVLG   "1H", 1
#define _TVPD   "1H", 10  //L/R PADDLE SELECT
#define _TVLN   "2J", 3   //L/R LINE SELECT

  // T/B select
#define _TL43   "3H", 6
#define _5TGTG  "1J", 12
#define _5TGBG  "4J", 6
#define _5THPG  "0J", 8
#define _THLG   "1H", 4
#define _THPD   "1H", 13  //T/B PADDLE SELECT
#define _THLN   "2J", 6   //T/B LINE SELECT

  // counters
#define _NCLA   "3F", 6
#define _NCL0   "3A", 14
#define _NCL1   "3A", 13
#define _NCL2   "3A", 12
#define _NCLC   "3A", 15

#define _NCRA   "3F", 8
#define _NCR0   "3C", 14
#define _NCR1   "3C", 13
#define _NCR2   "3C", 12
#define _NCRC   "3C", 15

#define _NCTA   "3F", 12
#define _NCT0   "3B", 14
#define _NCT1   "3B", 13
#define _NCT2   "3B", 12
#define _NCTC   "3B", 15

#define _NCBA   "4F", 6
#define _NCB0   "3D", 14
#define _NCB1   "3D", 13
#define _NCB2   "3D", 12
#define _NCBC   "3D", 15

//END OF GAME
#define _5NCFA  "4J", 8
#define _5NCFB  "4H", 6
#define _NCFC   "3J", 10

//PLAYER 1
#define _5NCFG  "3J", 4
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//PLAYER 2
#define _5NCAD  "4J", 12
#define _5NCFE  "4H", 8
#define _NCFF   "3J", 13

//number generation
#define _NCS2   "4A", 7
#define _NCS1   "4A", 9
#define _NCS0   "4B", 7
#define _NCSC   "4B", 9
#define _5NCS2  "4C", 2
#define _5NCS1  "4C", 4
#define _5NCS0  "4C", 6
#define _5NCG3  "4C", 8
#define _5NCG2  "4C", 10
#define _N999   VCC   //"4C", 12
#define _NCG7   "4D", 9
#define _NCG6   "4D", 7
#define _NCG5   "4D", 6
#define _NCG4   "4D", 5
#define _NCG3   "4D", 4
#define _NCG2   "4D", 3
#define _5NCGA  "4H", 3
#define _NCH7   "5D", 6
#define _NCH6   "5D", 8
#define _NCCE   "4G", 1
#define _5NCCE  "2C", 12
#define _NCC1   "3E", 13
#define _NCC2   "3E", 12
#define _NCC3   "3E", 11
#define _5NCCC  "1F", 11
#define _NCVD   "4E", 13


/* Page 2 */

//RECLOCK PADDLE POS & INTERSECT

#define _PKE8   "5G", 2
#define _PKL8   "5G", 5
#define _PKE5   "5G", 7
#define _PKL5   "5G", 10
#define _KABC   "5G", 12
#define _KABD   "5G", 15
#define _5PKE8  "6C", 2
#define _5PKL8  "6C", 4
#define _5PKE5  "6C", 6
#define _5PKL5  "6C", 8

//LEFT PADDLE POSITION
#define _PCLB   "2K", 5
#define _5PCLB  "2K", 6
#define _PCLE   "4F", 8
#define _PCL1   "6E", 13
#define _PCL2   "6E", 12
#define _PCL3   "6E", 11
#define _PCLC   "6E", 15

//RIGHT PADDLE POSITION
#define _PCRB   "2K", 9
#define _5PCRB  "2K", 7
#define _PCRE   "5F", 6
#define _PCR1   "6F", 13
#define _PCR2   "6F", 12
#define _PCR3   "6F", 11
#define _PCRC   "6F", 15

//TOP PADDLE POSITION
#define _PCTB   "7K", 5
#define _5PCTB  "7K", 6
#define _PCTE   "5F", 8
#define _PCT1   "6G", 13
#define _PCT2   "6G", 12
#define _PCT3   "6G", 11
#define _PCTC   "6G", 15

//BOTTOM PADDLE POSITION
#define _PCBB   "7K", 9
#define _5PCBB  "7K", 7
#define _PCBE   "5F", 12
#define _PCB1   "6D", 13
#define _PCB2   "6D", 12
#define _PCB3   "6D", 11
#define _PCBC   "6D", 15

//2 PLAYER PADDLE MULTIPLEXER
#define _PCSE   "5C", 7
#define _PCS3   "5C", 9
#define _PCS2   "5B", 7
#define _PCS1   "5B", 9
#define _5PJC1  "6A", 4
#define _5PCX3  "2M", 10
#define _1PCX3  "6B", 11

//REBOUND CONTROL
#define _PDPS   "5A", 2
#define _PDS3   "5A", 5
#define _PDS2   "5A", 7
#define _PDS1   "5A", 10
#define _PJC0   "5A", 12
#define _PJC1   "5A", 15
#define _5PDPS  "6C", 10
#define _5PCS3  "6C", 12

//DIRECTION CHANGE
#define _PDGS   "6J", 5
#define _5PDGS  "6J", 6
#define _5PDLC  "5E", 6
#define _5PDEC  "5E", 8

//GAME FLAG
#define _PGSC   "5H", 5
#define _5PGSC  "5H", 6
#define _5PGSR  "5E", 11

// 2/4 PLAYER INDICATOR
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#define _1PGSB  "6A", 6

//COIN COUNT
#define _PGCC   "5J", 5
#define _5PGCC  "5J", 6

// 2 PLAYERS DETECT
#define _PGCD   "4G", 4
#define _PGCE   "5J", 9
#define _5PGCE  "5J", 7

// 4 PLAYERS DETECT
#define _PGCF   "6H", 1
#define _PGCH   "6H", 4
#define _PGCG   "5H", 9
#define _5PGCG  "5H", 7

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//REBOUND DIRECTION CONTROL
#define _5BDSR  "8G", 3
#define _5BDSL  "8G", 6
#define _BDRR   "8F", 5
#define _5BDRR  "8F", 6
#define _5BDGR  "9J", 3
#define _5BDSD  "8G", 8
#define _5BDSU  "8G", 11
#define _BDRD   "8F", 9
#define _5BDRD  "8F", 7
#define _5BDGD  "9J", 8
#define _BGS3   "9J", 6

//BALL SPEED
#define _BSC2   "7J", 14
#define _BSC3   "7J", 13
#define _BSC4   "7J", 12
#define _5BSCG  "9H", 3
#define _BSCD   "9E", 1

// L/R T/B SELECTOR
#define _BDEC   "8H", 4
#define _5BDEC  "8H", 7
#define _BDLC   "8H", 9
#define _5BDLC  "8H", 12

//VELOCITY GEN FROM REBOUND ADDRESS
#define _BXYZ   "9H", 11
#define _BGS2   "7F", 4
#define _BGS1   "7F", 7
#define _BGS0   "7F", 9

//BASIC CONTROL OF BALL MOVEMENT
#define _BPE3   "7G", 9
#define _BPE2   "7G", 7
#define _BPE1   "7G", 6
#define _BPE0   "7G", 5
#define _BPL3   "7G", 4
#define _BPL2   "7G", 3
#define _BPL1   "7G", 2
#define _BPL0   "7G", 1

//HORIZ & VERT BALL MOVEMENT MULTIPLEXER
#define _BPSV   "3H", 8
#define _BPSC   "3H", 11
#define _BPS3   "7H", 4
#define _BPS2   "7H", 7
#define _BPS1   "7H", 9
#define _BPS0   "7H", 12

//INTERCEPT DIRECTION DEFINITION
#define _5KBCH  "6H", 10
#define _KACA   "9H", 6
#define _5KBDG  "6H", 13
#define _KACB   "9H", 8

//INTERSECT CLOCK
#define _2KQEA  "9D", 1

//BOUNDERY INTERSECT
#define _KACE   "9F", 6

//PADDLE OR CROSS INTERSECT
#define _KACF   "9F", 11

//SCORE
#define _KXYA   "9E", 13
#define _5KACG  "9G", 8
#define _5KACH  "9G", 11
#define _KADG   "9F", 3

//ball intercepts vert pad & horz cross
#define _5KAAA  "4G", 10
#define _KAAC   "9E", 4  

//ball intercepts vert cross & horz pad
#define _5KAAB  "4G", 13
#define _KAAD   "9E", 10  


//INTERCEPT
#define _5KAAE  "9G", 3  //ball intercept vert line
#define _5KAAF  "9G", 6  //ball intercept horiz line
#define _KAAG   "2J", 8  //ball intercept top & bottom scoring regions
#define _KAAH   "2J", 11 //ball intercept left & right scoring regions

//RECLOCK
#define _5KABE  "8J", 2
#define _5KABF  "8J", 5
#define _KABG   "8J", 7
#define _KABH   "8J", 10
#define _5VDAF  "8J", 12
#define _VDSC   "8J", 15

#define _5KABC  "6A", 8
#define _5KABD  "6A", 10

//
#define _6KQCA  "9F", 8
#define _2KQLN  "9D", 4
#define _2KQEL  "9D", 10
#define _7KQPD  "9D", 13
#define _KAYA   "2M", 13

//COMPOSITE VIDEO
#define _5VDAC  "4F", 12
#define _VDAD   "3G", 8
#define _5VDAE  "4H", 11

#define _5VDS0  "2H", 10
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//BALL GENERATION AND CONTROL
  //horiz
#define _5BECL  "9C", 6
#define _BECA   "7E", 15
#define _BECB   "7D", 15
#define _5BECB  "8A", 4
#define _5BEGA  "8C", 2
#define _5BEGB  "8C", 5
#define _5BEGC  "8C", 7
#define _5BEGD  "8C", 10
#define _PGCB   "8C", 12
#define _1PGCC  "8C", 15
#define _1BEGD  "8A", 8
  //vert
#define _5BLCL  "9A", 3
#define _BLCA   "8E", 15
#define _BLCB   "8D", 15
#define _5BLCB  "8A", 6
#define _5BLGA  "8B", 2
#define _5BLGB  "8B", 5
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
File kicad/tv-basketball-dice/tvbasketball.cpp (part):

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    VIDEO_RESISTANCE(2, K_OHM(2.2))
    VIDEO_RESISTANCE(3, K_OHM(1.8))
    VIDEO_RESISTANCE(4, K_OHM(1.0))
    VIDEO_RESISTANCE(Video::HBLANK_PIN, K_OHM(1.2))
    VIDEO_CONTRAST(1.5)
    VIDEO_RETRO_V_SIZE(246)
VIDEO_DESC_END
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	#define H2  "15H", 9
	#define H4  "15H", 8
	#define H8  "15H", 11
	#define H4_n  "15J", 6
	#define H8_n  "15J", 4

	#define H16  "14H", 12
	#define H32  "14H", 9
	#define H64  "14H", 8
	#define H128  "14H", 11
	#define H64_n  "10D", 11
	#define H16_n  "15J", 2
	
	#define H256  "14J", 3
	#define H256_n  "14J", 2
	
	#define HBLANK  "13H", 6
	#define HBLANK_n  "13H", 3
	#define HSYNC_n  "13H", 8
	
	#define V1  "11F", 12
	#define V2  "11F", 9
	#define V4  "11F", 8
	#define V8  "11F", 11
	#define V2_n  "12F", 8
	#define V4_n  "12J", 6
	#define V8_n  "12F", 12
	
	#define V16  "11G", 12
	#define V32  "11G", 9
	#define V64  "11G", 8
	#define V128  "11G", 11
	#define V256  "11J", 5
	#define V16_n  "12F", 6
	#define V64_n  "12F", 4
	#define V128_n  "12F", 10
	
    #define VRESET "12G", 8
	#define VBLANK  "11E", 4
	#define VSYNC_n  "12H", 6	
	
    #define BALL "10J", 1

    #define GAME_ON "10B", 10


	/**************************************************************************
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    CONNECTION("VIDEO", 3, "10D", 3)
    CONNECTION("VIDEO", 4, "15D", 10)

    CONNECTION("VIDEO", Video::HBLANK_PIN, HBLANK)
    CONNECTION("VIDEO", Video::VBLANK_PIN, VBLANK)


#ifdef DEBUG
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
